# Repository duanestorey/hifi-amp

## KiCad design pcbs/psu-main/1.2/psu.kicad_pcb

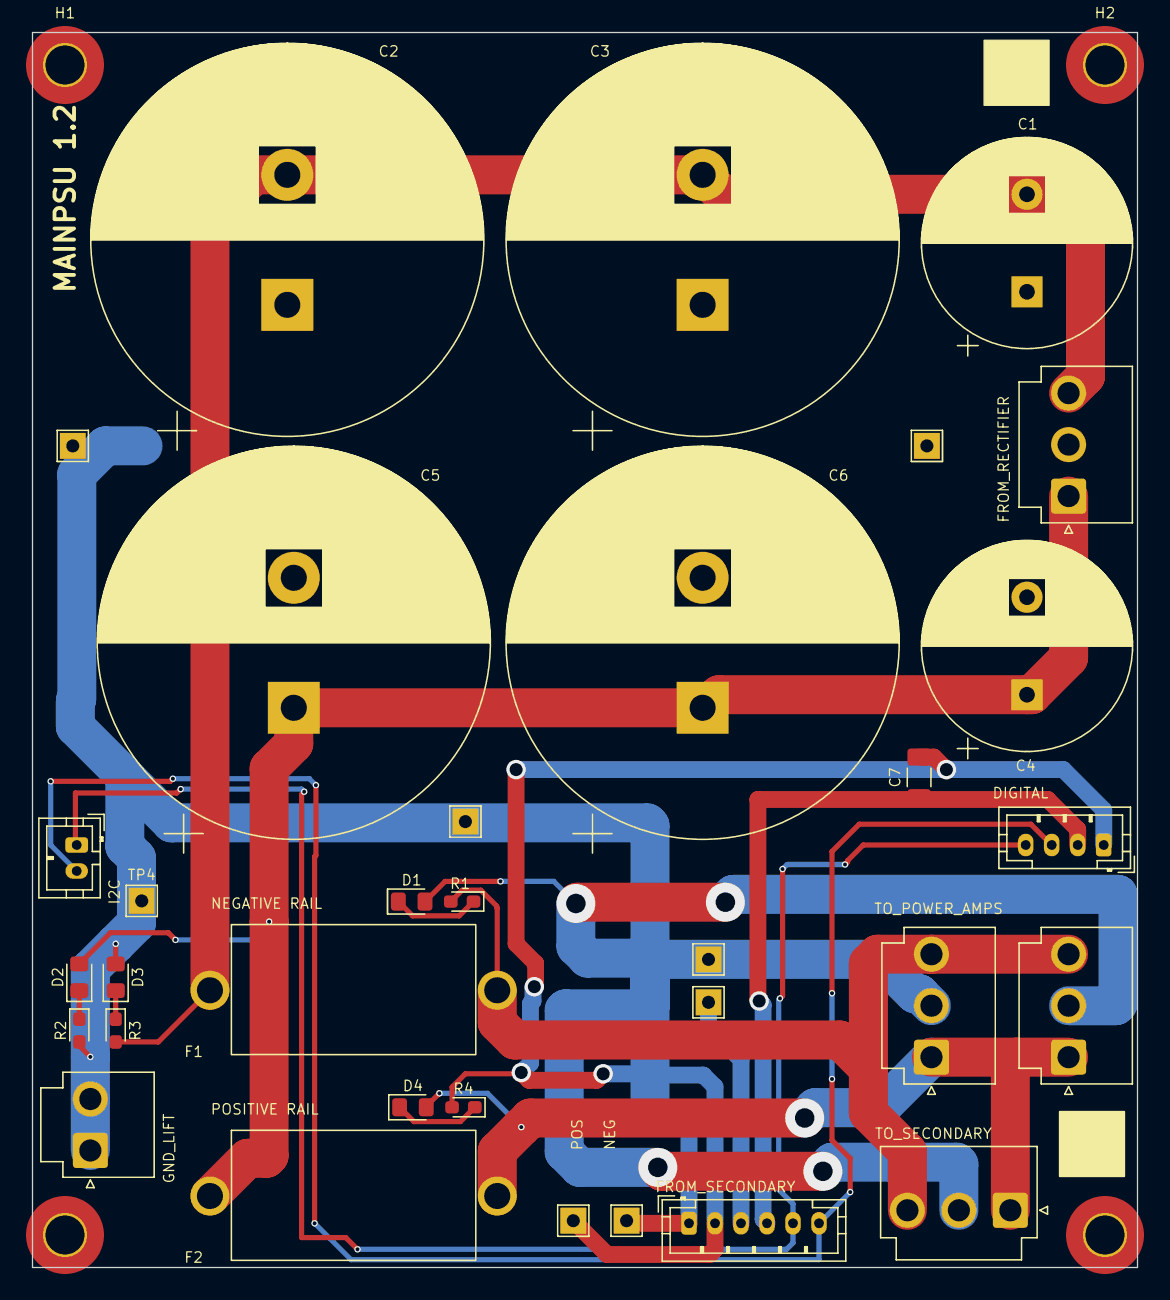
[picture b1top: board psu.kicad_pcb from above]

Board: 2 copper layers, 85.0 x 95.0 mm, 37 parts (0 on the bottom side), 12 nets.

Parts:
C1, C4: 3300u 50V; CP_Radial_D16.0mm_P7.50mm
C2, C3, C5, C6: 15000U; CP_Radial_D30.0mm_P10.00mm_SnapIn
C7: 10u; C_1206_3216Metric_Pad1.33x1.80mm_HandSolder
D1, D3: BLUE; LED_0805_2012Metric_Pad1.15x1.40mm_HandSolder
D2, D4: YELLOW; LED_0805_2012Metric_Pad1.15x1.40mm_HandSolder
F1, F2: Fuse_Small; Aliexpress Fuse 5x20
H1, H2, H3, H4: MountingHole; MountingHole_3mm_Pad_TopOnly
J1, J4, J5, J7: Conn_01x03_Male; JST_VH_B3P-VH_1x03_P3.96mm_Vertical
J2: Conn_01x02_Pin; JST_PH_B2B-PH-K_1x02_P2.00mm_Vertical
J3: Conn_01x04_Pin; JST_PH_B4B-PH-K_1x04_P2.00mm_Vertical
J6: Conn_01x02_Male; JST_VH_B2P-VH-B_1x02_P3.96mm_Vertical
J8: Conn_01x06_Pin; JST_PH_B6B-PH-K_1x06_P2.00mm_Vertical
R1, R2, R3, R4: 16K; LED_0603_1608Metric_Pad1.05x0.95mm_HandSolder
TP1, TP2, TP3, TP4, TP5, TP6, TP7, TP8: TestPoint; TestPoint_THTPad_2.0x2.0mm_Drill1.0mm

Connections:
3V3: C7.1, J3.2, J8.4
unnamed: D1.1 (K), R1.1
unnamed: D2.1 (K), R2.1
unnamed: D3.1 (K), R3.1
unnamed: D4.1 (K), R4.1
PGND: C1.1, C2.1, C3.1, C4.2, C5.2, C6.2, C7.2, D1.2 (A), D3.2 (A), J1.2, J3.1, J4.2, J5.2, J6.1, J6.2, J7.2, J8.1, J8.2, J8.3, R2.2, R4.2, TP1.1, TP2.1, TP3.1, TP4.1, TP5.1, TP6.1, TP7.1, TP8.1
SCL: J2.1, J3.4, J8.5
SDA: J2.2, J3.3, J8.6
VM1: C1.2, C2.2, C3.2, F1.1, J1.3, R3.2
VNOUT: F1.2, J4.3, J5.3, J7.3, R1.2
VP1: C4.1, C5.1, C6.1, D2.2 (A), F2.1, J1.1
VPOUT: D4.2 (A), F2.2, J4.1, J5.1, J7.1

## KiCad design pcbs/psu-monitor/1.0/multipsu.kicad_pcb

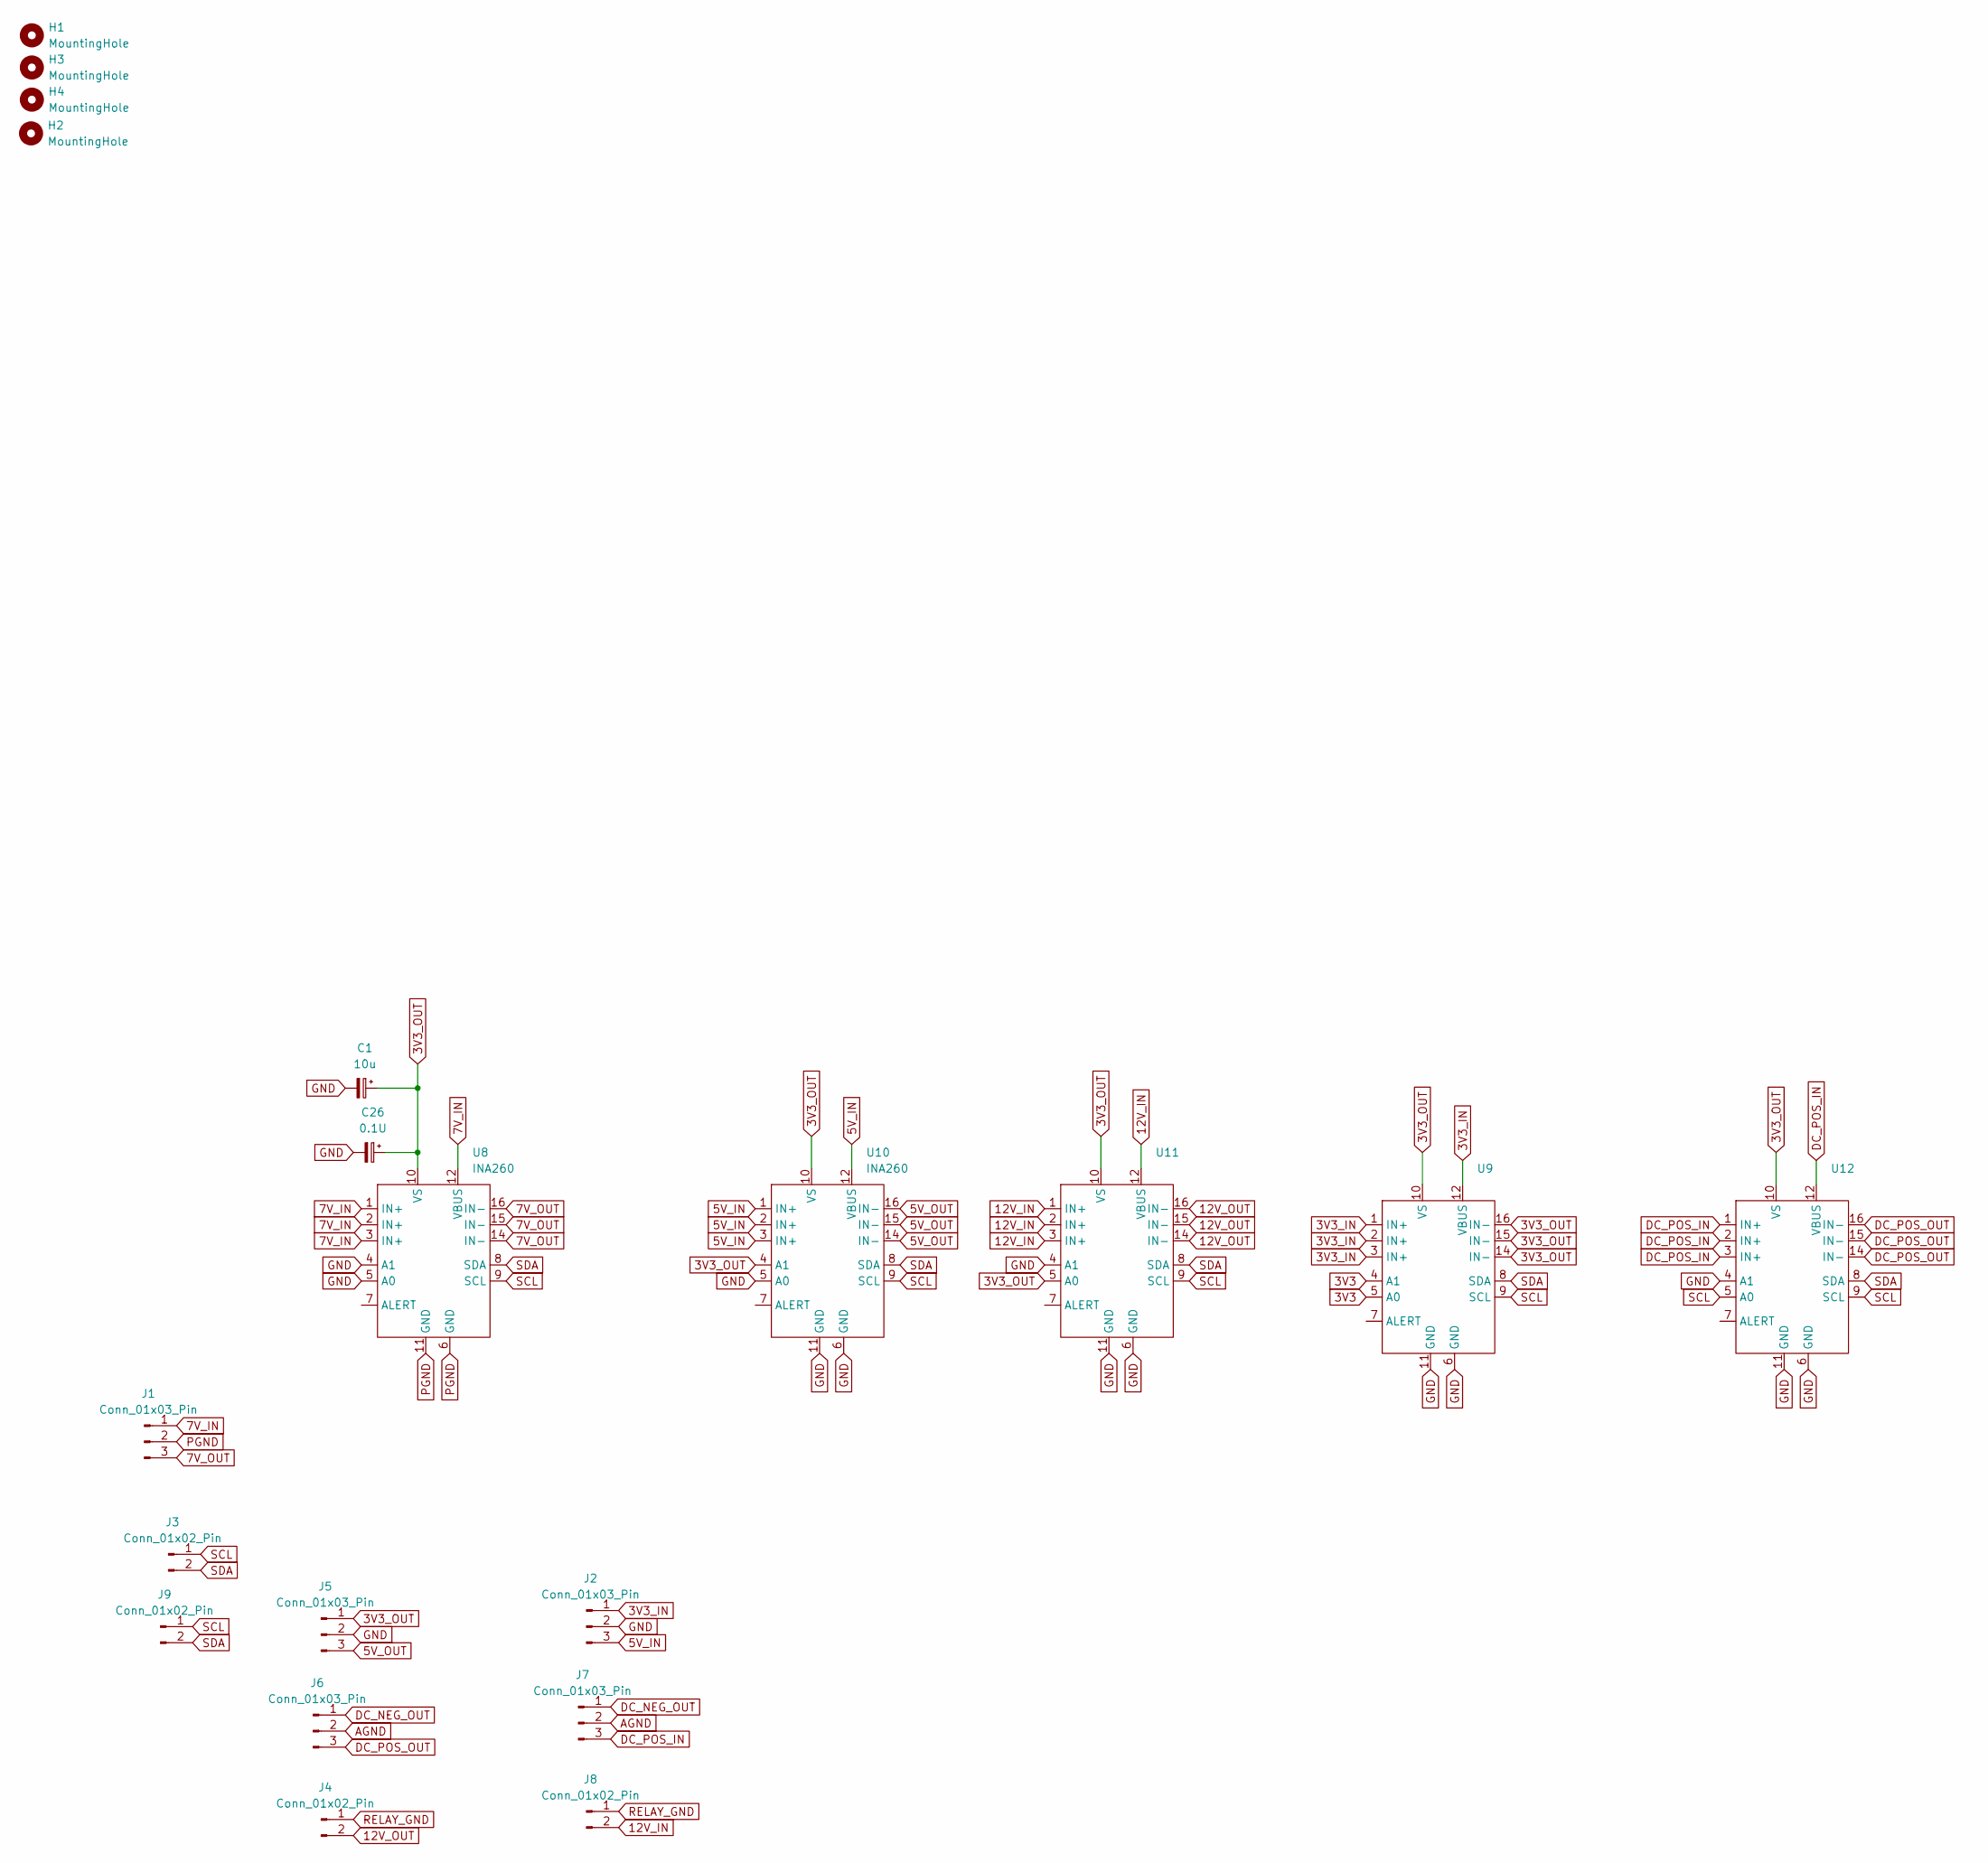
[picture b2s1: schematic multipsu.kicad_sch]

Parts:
C1: 10u; C_1206_3216Metric_Pad1.33x1.80mm_HandSolder
C26: 0.1U; C_0603_1608Metric_Pad1.08x0.95mm_HandSolder
H1, H2, H3, H4: MountingHole; MountingHole_3.2mm_M3_DIN965_Pad_TopOnly
J1, J2, J5, J6, J7: Conn_01x03_Pin; JST_PH_B3B-PH-K_1x03_P2.00mm_Vertical
J3, J4, J8, J9: Conn_01x02_Pin; JST_PH_B2B-PH-K_1x02_P2.00mm_Vertical
U8, U9, U10, U11, U12: INA260; TSSOP-16_4.4x5mm_P0.65mm

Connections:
3V3: U9.4 (A1), U9.5 (A0)
3V3_IN: J2.1, U9.1 (IN+), U9.2 (IN+), U9.3 (IN+), U9.12 (VBUS)
3V3_OUT: C1.1, C26.1, J5.1, U8.10 (VS), U9.10 (VS), U9.14 (IN-), U9.15 (IN-), U9.16 (IN-), U10.4 (A1), U10.10 (VS), U11.5 (A0), U11.10 (VS), U12.10 (VS)
5V_IN: J2.3, U10.1 (IN+), U10.2 (IN+), U10.3 (IN+), U10.12 (VBUS)
5V_OUT: J5.3, U10.14 (IN-), U10.15 (IN-), U10.16 (IN-)
7V_IN: J1.1, U8.1 (IN+), U8.2 (IN+), U8.3 (IN+), U8.12 (VBUS)
7V_OUT: J1.3, U8.14 (IN-), U8.15 (IN-), U8.16 (IN-)
12V_IN: J8.2, U11.1 (IN+), U11.2 (IN+), U11.3 (IN+), U11.12 (VBUS)
12V_OUT: J4.2, U11.14 (IN-), U11.15 (IN-), U11.16 (IN-)
AGND: J6.2, J7.2
DC_NEG_OUT: J6.1, J7.1
DC_POS_IN: J7.3, U12.1 (IN+), U12.2 (IN+), U12.3 (IN+), U12.12 (VBUS)
DC_POS_OUT: J6.3, U12.14 (IN-), U12.15 (IN-), U12.16 (IN-)
GND: C1.2, C26.2, J2.2, J5.2, U8.4 (A1), U8.5 (A0), U9.6 (GND), U9.11 (GND), U10.5 (A0), U10.6 (GND), U10.11 (GND), U11.4 (A1), U11.6 (GND), U11.11 (GND), U12.4 (A1), U12.6 (GND), U12.11 (GND)
PGND: J1.2, U8.6 (GND), U8.11 (GND)
RELAY_GND: J4.1, J8.1
SCL: J3.1, J9.1, U8.9 (SCL), U9.9 (SCL), U10.9 (SCL), U11.9 (SCL), U12.5 (A0), U12.9 (SCL)
SDA: J3.2, J9.2, U8.8 (SDA), U9.8 (SDA), U10.8 (SDA), U11.8 (SDA), U12.8 (SDA)

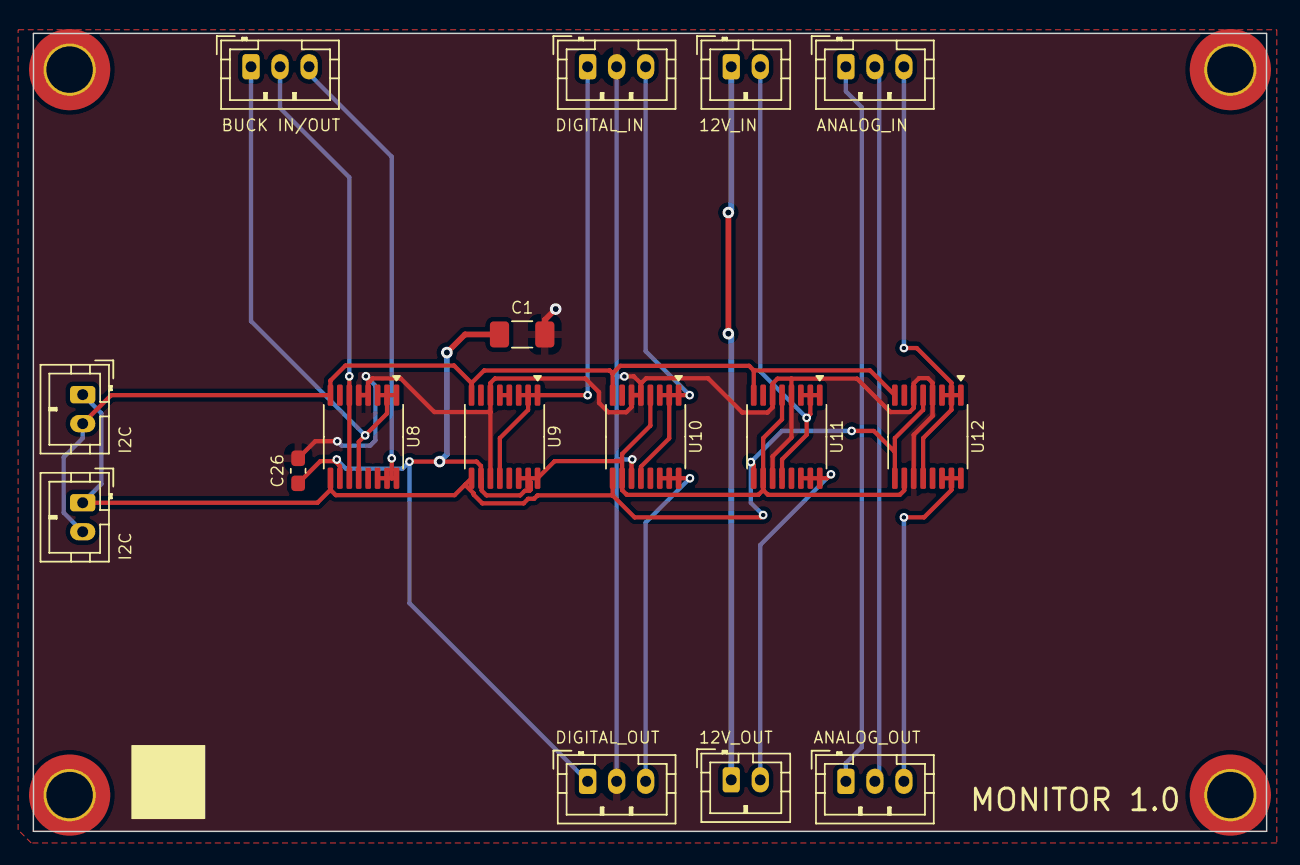
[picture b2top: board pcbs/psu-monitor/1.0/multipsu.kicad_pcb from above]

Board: 2 copper layers, 85.0 x 55.0 mm, 20 parts (0 on the bottom side), 18 nets.

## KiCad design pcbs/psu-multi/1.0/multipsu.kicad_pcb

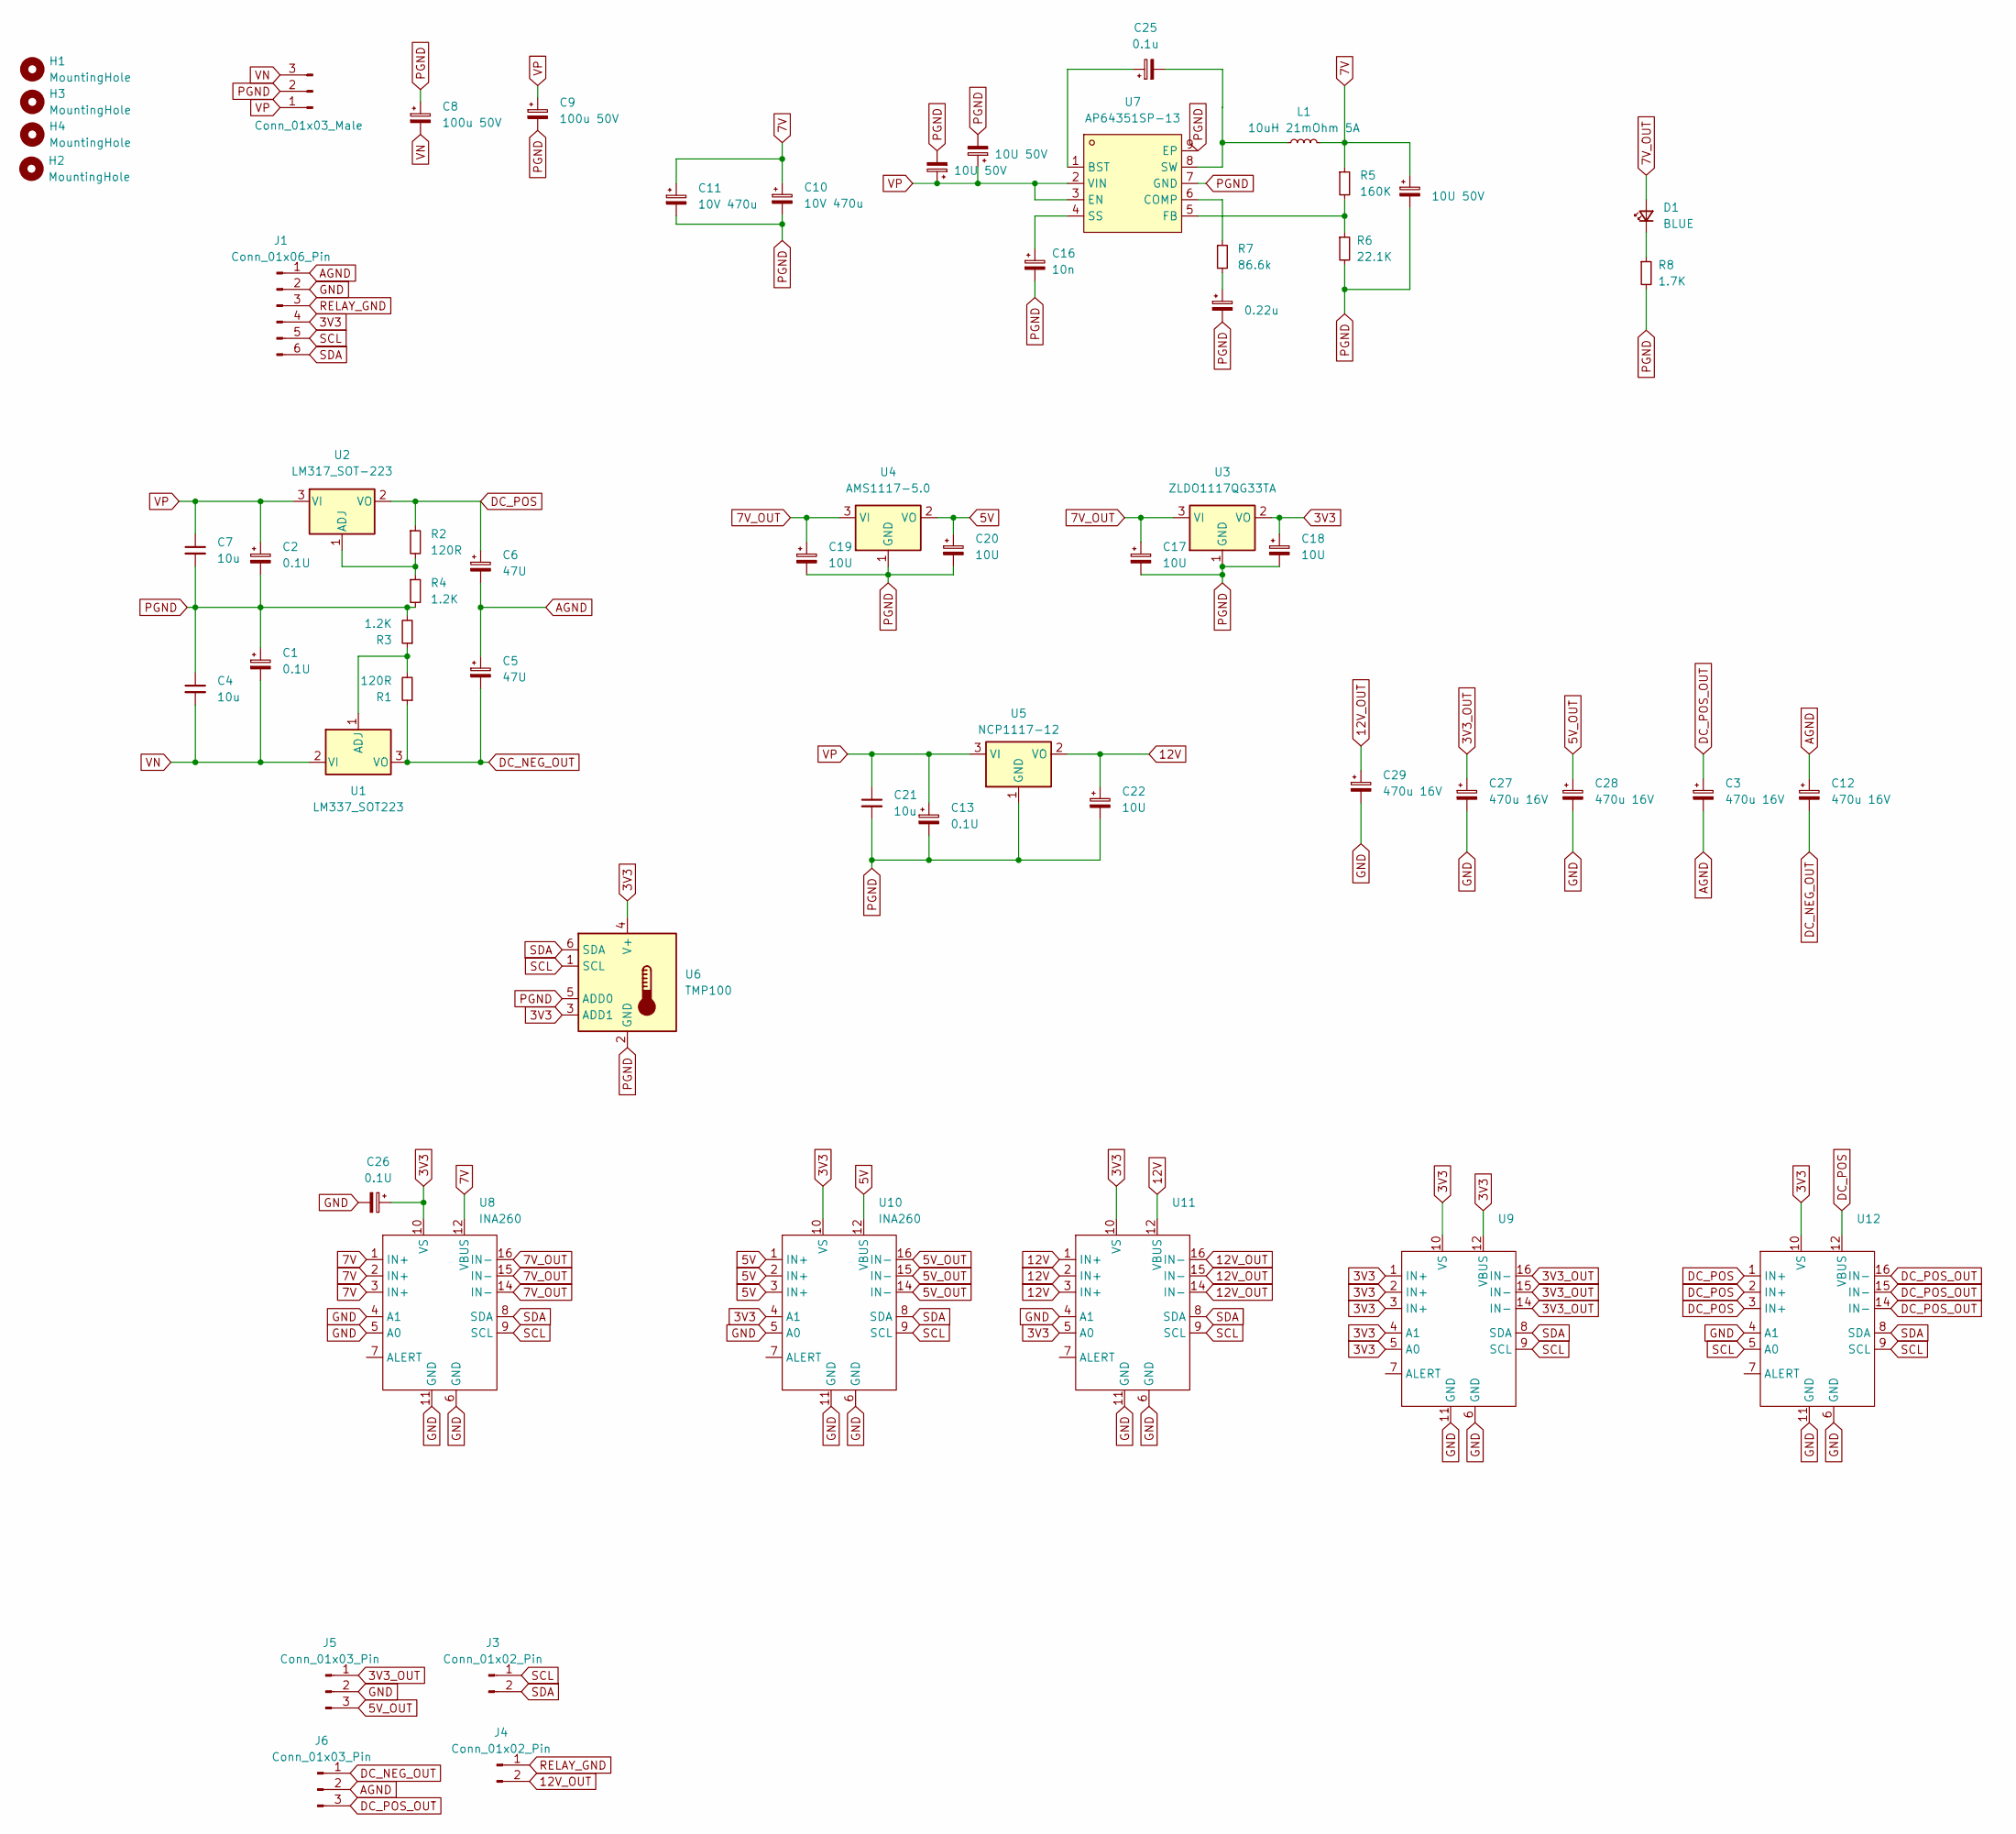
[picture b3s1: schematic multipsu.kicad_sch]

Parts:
C1, C2, C13, C26: 0.1U; C_0603_1608Metric_Pad1.08x0.95mm_HandSolder
C3, C12, C27, C28, C29: 470u 16V; CP_Radial_D6.3mm_P2.50mm
C4, C7, C21: 10u; C_1206_3216Metric_Pad1.33x1.80mm_HandSolder
C5, C6: 47U; C_1206_3216Metric_Pad1.33x1.80mm_HandSolder
C8, C9: 100u 50V; CP_Radial_D8.0mm_P3.50mm
C10, C11: 10V 470u; CP_Radial_D8.0mm_P3.50mm
C14, C23, C24: 10U 50V; C_1206_3216Metric_Pad1.33x1.80mm_HandSolder
C15: 0.22u; C_0805_2012Metric_Pad1.18x1.45mm_HandSolder
C16: 10n; C_0805_2012Metric_Pad1.18x1.45mm_HandSolder
C17, C18, C19, C20, C22: 10U; C_1206_3216Metric_Pad1.33x1.80mm_HandSolder
C25: 0.1u; C_0805_2012Metric_Pad1.18x1.45mm_HandSolder
D1: BLUE; LED_0805_2012Metric_Pad1.15x1.40mm_HandSolder
H1, H2, H3, H4: MountingHole; MountingHole_3.2mm_M3_DIN965_Pad_TopOnly
J1: Conn_01x06_Pin; JST_PH_B6B-PH-K_1x06_P2.00mm_Vertical
J2: Conn_01x03_Male; JST_VH_B3P-VH_1x03_P3.96mm_Vertical
J3, J4: Conn_01x02_Pin; JST_PH_B2B-PH-K_1x02_P2.00mm_Vertical
J5, J6: Conn_01x03_Pin; JST_PH_B3B-PH-K_1x03_P2.00mm_Vertical
L1: 10uH 21mOhm 5A; L_Vishay_IHLP-4040; Mouser 704-DR1040-7R0-R
R1, R2: 120R; R_0603_1608Metric_Pad0.98x0.95mm_HandSolder
R3, R4: 1.2K; R_0603_1608Metric_Pad0.98x0.95mm_HandSolder
R5: 160K; R_0603_1608Metric_Pad0.98x0.95mm_HandSolder; Mouser 603-RC0603JR-10180KL
R6: 22.1K; R_0603_1608Metric_Pad0.98x0.95mm_HandSolder; Mouser 603-RC0603JR-07820KP
R7: 86.6k; R_0603_1608Metric_Pad0.98x0.95mm_HandSolder; Mouser 71-CRCW0603-86.6K-E3
R8: 1.7K; R_0603_1608Metric_Pad0.98x0.95mm_HandSolder; Mouser 603-RC0603JR-07820KP
U1: LM337_SOT223; SOT-223-3_TabPin2; Mouser 926-LM337IMPX/NOPB
U2: LM317_SOT-223; SOT-223-3_TabPin2; Mouser 595-LM317DCY
U3: ZLDO1117QG33TA; SOT-223-3_TabPin2; Mouser ZLDO1117QG33TA
U4: AMS1117-5.0; SOT-223-3_TabPin2; Mouser 926-LM1117MPX5.0NOPB
U5: NCP1117-12; SOT-223; Mouser 863-NCP1117ST12T3G
U6: TMP100; SOT-23-6
U7: AP64351SP-13; SOIC-8_L4.9-W3.9-P1.27-LS6.0-BL-EP; LCSC Part C3192339
U8, U9, U10, U11, U12: INA260; TSSOP-16_4.4x5mm_P0.65mm

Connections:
3V3: C18.1, C26.1, J1.4, U3.2 (VO), U6.3 (ADD1), U6.4 (V+), U8.10 (VS), U9.1 (IN+), U9.2 (IN+), U9.3 (IN+), U9.4 (A1), U9.5 (A0), U9.10 (VS), U9.12 (VBUS), U10.4 (A1), U10.10 (VS), U11.5 (A0), U11.10 (VS), U12.10 (VS)
3V3_OUT: C27.1, J5.1, U9.14 (IN-), U9.15 (IN-), U9.16 (IN-)
5V: C20.1, U4.2 (VO), U10.1 (IN+), U10.2 (IN+), U10.3 (IN+), U10.12 (VBUS)
5V_OUT: C28.1, J5.3, U10.14 (IN-), U10.15 (IN-), U10.16 (IN-)
7V: C10.1, C11.1, C14.1, L1.2, R5.1, U8.1 (IN+), U8.2 (IN+), U8.3 (IN+), U8.12 (VBUS)
7V_OUT: C17.1, C19.1, D1.2 (A), U3.3 (VI), U4.3 (VI), U8.14 (IN-), U8.15 (IN-), U8.16 (IN-)
12V: C22.1, U5.2 (VO), U11.1 (IN+), U11.2 (IN+), U11.3 (IN+), U11.12 (VBUS)
12V_OUT: C29.1, J4.2, U11.14 (IN-), U11.15 (IN-), U11.16 (IN-)
AGND: C3.2, C5.1, C6.2, C12.1, J1.1, J6.2
DC_NEG_OUT: C5.2, C12.2, J6.1, R1.1, U1.3 (VO)
DC_POS: C6.1, R2.1, U2.2 (VO), U12.1 (IN+), U12.2 (IN+), U12.3 (IN+), U12.12 (VBUS)
DC_POS_OUT: C3.1, J6.3, U12.14 (IN-), U12.15 (IN-), U12.16 (IN-)
GND: C26.2, C27.2, C28.2, C29.2, J1.2, J5.2, U8.4 (A1), U8.5 (A0), U8.6 (GND), U8.11 (GND), U9.6 (GND), U9.11 (GND), U10.5 (A0), U10.6 (GND), U10.11 (GND), U11.4 (A1), U11.6 (GND), U11.11 (GND), U12.4 (A1), U12.6 (GND), U12.11 (GND)
unnamed: C15.1, R7.2
unnamed: D1.1 (K), R8.1
unnamed: R1.2, R3.1, U1.1 (ADJ)
unnamed: R2.2, R4.1, U2.1 (ADJ)
unnamed: C25.1, U7.1 (BST)
unnamed: R7.1, U7.6 (COMP)
unnamed: R5.2, R6.1, U7.5 (FB)
unnamed: C16.1, U7.4 (SS)
unnamed: C25.2, L1.1, U7.8 (SW)
PGND: C1.1, C2.2, C4.1, C7.2, C8.1, C9.2, C10.2, C11.2, C13.2, C14.2, C15.2, C16.2, C17.2, C18.2, C19.2, C20.2, C21.2, C22.2, C23.2, C24.2, J2.2, R3.2, R4.2, R6.2, R8.2, U3.1 (GND), U4.1 (GND), U5.1 (GND), U6.2 (GND), U6.5 (ADD0), U7.7 (GND), U7.9 (EP)
RELAY_GND: J1.3, J4.1
SCL: J1.5, J3.1, U6.1 (SCL), U8.9 (SCL), U9.9 (SCL), U10.9 (SCL), U11.9 (SCL), U12.5 (A0), U12.9 (SCL)
SDA: J1.6, J3.2, U6.6 (SDA), U8.8 (SDA), U9.8 (SDA), U10.8 (SDA), U11.8 (SDA), U12.8 (SDA)
VN: C1.2, C4.2, C8.2, J2.3, U1.2 (VI)
VP: C2.1, C7.1, C9.1, C13.1, C21.1, C23.1, C24.1, J2.1, U2.3 (VI), U5.3 (VI), U7.2 (VIN), U7.3 (EN)

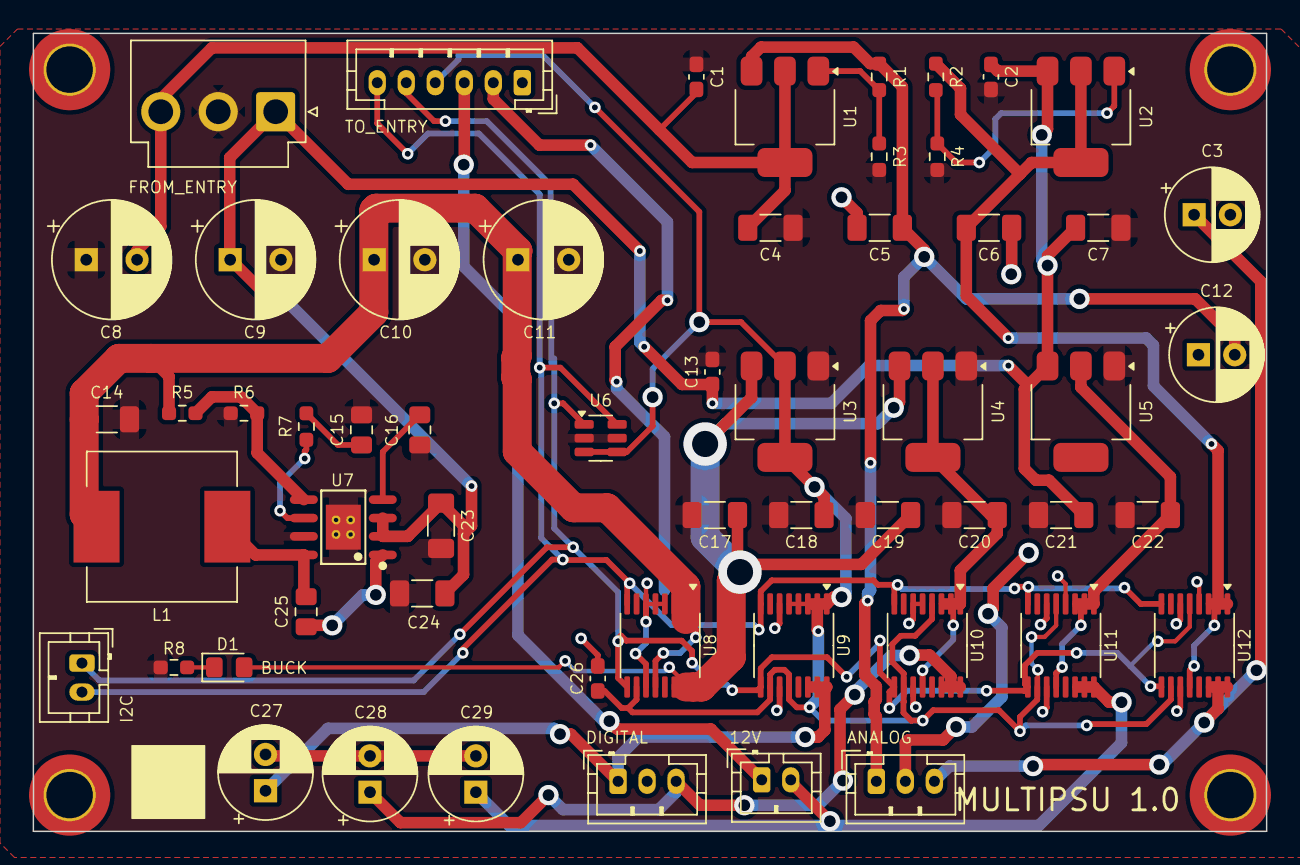
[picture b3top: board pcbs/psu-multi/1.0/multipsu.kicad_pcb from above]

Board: 2 copper layers, 85.0 x 55.0 mm, 61 parts (0 on the bottom side), 28 nets.

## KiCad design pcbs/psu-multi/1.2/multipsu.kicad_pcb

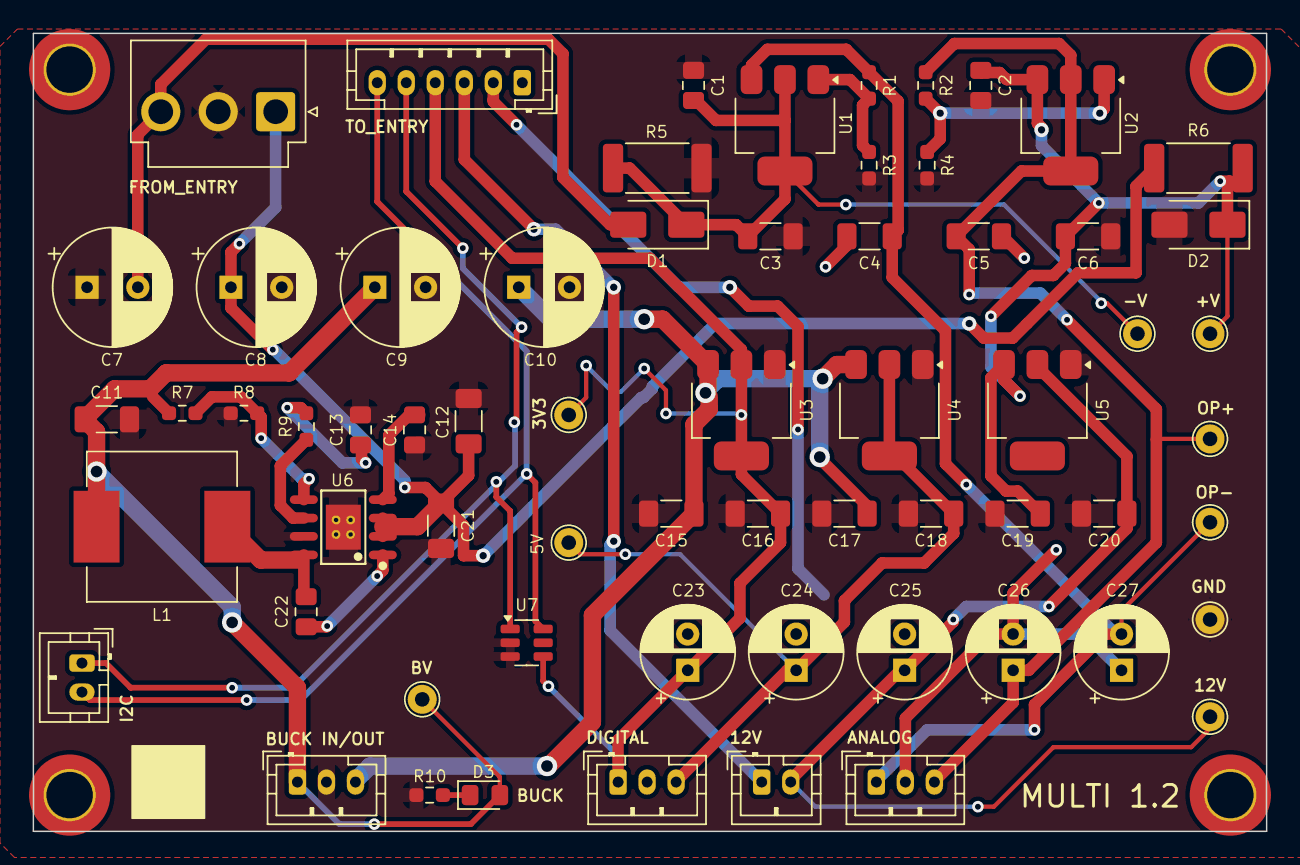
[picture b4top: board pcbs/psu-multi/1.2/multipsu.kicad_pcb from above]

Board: 2 copper layers, 85.0 x 55.0 mm, 68 parts (0 on the bottom side), 26 nets.

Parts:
C1, C2: 0.1U; C_0805_2012Metric_Pad1.18x1.45mm_HandSolder
C3, C6, C19: 10u; C_1206_3216Metric_Pad1.33x1.80mm_HandSolder
C4, C5, C15, C16, C17, C18, C20: 10U; C_1206_3216Metric_Pad1.33x1.80mm_HandSolder
C7, C8: 100u 50V; CP_Radial_D8.0mm_P3.50mm
C9, C10: 1000u 16V; CP_Radial_D8.0mm_P3.50mm
C11, C12, C21: 10U 50V; C_1206_3216Metric_Pad1.33x1.80mm_HandSolder
C13: 0.22u; C_0805_2012Metric_Pad1.18x1.45mm_HandSolder
C14: 0.01u; C_0805_2012Metric_Pad1.18x1.45mm_HandSolder
C22: 0.1u; C_0805_2012Metric_Pad1.18x1.45mm_HandSolder
C23, C24, C25, C26, C27: 220u 16V; CP_Radial_D6.3mm_P2.50mm
D1, D2: 16V; D_SMA
D3: BLUE; LED_0805_2012Metric_Pad1.15x1.40mm_HandSolder
H1, H2, H3, H4: MountingHole; MountingHole_3.2mm_M3_DIN965_Pad_TopOnly
J1: Conn_01x06_Pin; JST_PH_B6B-PH-K_1x06_P2.00mm_Vertical
J2: Conn_01x03_Male; JST_VH_B3P-VH_1x03_P3.96mm_Vertical
J3, J6: Conn_01x02_Pin; JST_PH_B2B-PH-K_1x02_P2.00mm_Vertical
J4, J5, J7: Conn_01x03_Pin; JST_PH_B3B-PH-K_1x03_P2.00mm_Vertical
L1: 10uH 21mOhm 5A; L_Vishay_IHLP-4040
R1, R2: 120R; R_0603_1608Metric_Pad0.98x0.95mm_HandSolder
R3, R4: 1.2K; R_0603_1608Metric_Pad0.98x0.95mm_HandSolder
R5, R6: 150R; R_2512_6332Metric_Pad1.40x3.35mm_HandSolder
R7: 160K; R_0603_1608Metric_Pad0.98x0.95mm_HandSolder
R8: 22.1K; R_0603_1608Metric_Pad0.98x0.95mm_HandSolder
R9: 86.6k; R_0603_1608Metric_Pad0.98x0.95mm_HandSolder
R10: 1.7K; R_0603_1608Metric_Pad0.98x0.95mm_HandSolder
TP1, TP2, TP3, TP4, TP5, TP6, TP7, TP8, TP9: TestPoint; TestPoint_THTPad_D2.0mm_Drill1.0mm
U1: LM337_SOT223; SOT-223-3_TabPin2
U2: LM317_SOT-223; SOT-223-3_TabPin2
U3: ZLDO1117QG33TA; SOT-223-3_TabPin2
U4: AMS1117-5.0; SOT-223-3_TabPin2
U5: NCP1117-12; SOT-223
U6: AP64351SP-13; SOIC-8_L4.9-W3.9-P1.27-LS6.0-BL-EP
U7: TMP100; SOT-23-6

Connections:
3V3: C16.1, C23.1, J1.4, J5.1, TP3.1, U3.2 (VO), U7.4 (V+)
5V: C18.1, C24.1, J5.3, TP6.1, U4.2 (VO)
7V_IN: C10.1, C15.1, C17.1, J4.3, U3.3 (VI), U4.3 (VI)
7V_OUT: C9.1, C11.1, D3.2 (A), J4.1, L1.2, R7.1, TP8.1
12V: C20.1, C25.1, J6.2, TP9.1, U5.2 (VO)
16V: C2.1, C6.1, C19.1, D2.1 (K), R6.2, TP2.1, U2.3 (VI), U5.3 (VI)
-16V: C1.2, C3.2, D1.1 (K), R5.2, TP1.1, U1.2 (VI)
AGND: C4.1, C5.2, C26.2, C27.1, J1.1, J7.2
DC_NEG: C4.2, C27.2, J7.1, R1.1, TP5.1, U1.3 (VO)
DC_POS: C5.1, C26.1, J7.3, R2.1, TP4.1, U2.2 (VO)
GND: C23.2, C24.2, C25.2, J1.2, J5.2
unnamed: C13.1, R9.2
unnamed: D3.1 (K), R10.1
unnamed: R1.2, R3.1, U1.1 (ADJ)
unnamed: R2.2, R4.1, U2.1 (ADJ)
unnamed: C22.1, U6.1 (BST)
unnamed: R9.1, U6.6 (COMP)
unnamed: R7.2, R8.1, U6.5 (FB)
unnamed: C14.1, U6.4 (SS)
unnamed: C22.2, L1.1, U6.8 (SW)
PGND: C1.1, C2.2, C3.1, C6.2, C7.1, C8.2, C9.2, C10.2, C11.2, C12.2, C13.2, C14.2, C15.2, C16.2, C17.2, C18.2, C19.2, C20.2, C21.2, D2.2 (A), J2.2, J4.2, R3.2, R4.2, R5.1, R8.2, R10.2, TP7.1, U3.1 (GND), U4.1 (GND), U5.1 (GND), U6.7 (GND), U6.9 (EP), U7.2 (GND), U7.3 (ADD1)
RELAY_GND: J1.3, J6.1
SCL: J1.5, J3.1, U7.1 (SCL)
SDA: J1.6, J3.2, U7.6 (SDA)
VN: C7.2, D1.2 (A), J2.3
VP: C8.1, C12.1, C21.1, J2.1, R6.1, U6.2 (VIN), U6.3 (EN)
